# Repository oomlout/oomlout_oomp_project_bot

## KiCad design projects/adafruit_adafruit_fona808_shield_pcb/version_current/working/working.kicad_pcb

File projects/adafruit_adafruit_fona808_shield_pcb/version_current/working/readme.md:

# OOMP Project  
## Adafruit-FONA808-Shield-PCB  by adafruit  
  
oomp key: oomp_projects_flat_adafruit_adafruit_fona808_shield_pcb  
(snippet of original readme)  
  
-- Adafruit FONA808 Shield PCB  
  
<a href="http://www.adafruit.com/products/2636"><br/>  
Click here to purchase one from the Adafruit shop</a>  
  
PCB files for the Adafruit FONA808 Shield. Format is EagleCAD schematic and board layout  
* https://www.adafruit.com/products/2636  
  
--- DESCRIPTION  
Cellular + GPS tracking, all in one, for your Arduino? Oh yes! Introducing Adafruit FONA 808 GSM + GPS Shield, an all-in-one cellular phone module with that lets you add location-tracking, voice, text, SMS and data to your project, in Arduino shield format for easy use.  
  
If you want a version without GPS, check out the FONA 800 Shield [here](https://www.adafruit.com/product/2468).  
  
If you don't need the shield format, we also have this is a petite breakout [here](https://www.adafruit.com/product/2542).  
  
If you just want a plain FONA, [click here](https://www.adafruit.com/product/1946).  
  
This shield fits right over your Arduino or compatible. At the heart is a powerful GSM cellular module (we use the latest SIM808) with integrated GPS. This module can do just about everything  
  
- Quad-band 850/900/1800/1900MHz - connect onto any global GSM network with any 2G SIM (in the USA, T-Mobile is suggested)  
- Fully-integrated GPS (MT3337 chipset with -165 dBm tracking sensitivity) that can be controlled and query over the same serial port  
- Make and receive voice calls using a headset or an external 32Ω speaker + electret microphone  
- Send and receive SM  
  full source readme at [readme_src.md](readme_src.md)  
  
source repo at: [https://github.com/adafruit/Adafruit-FONA808-Shield-PCB](https://github.com/adafruit/Adafruit-FONA808-Shield-PCB)  
## Board  

## Schematic  

[schematic pdf](working_schematic.pdf)  
## Images

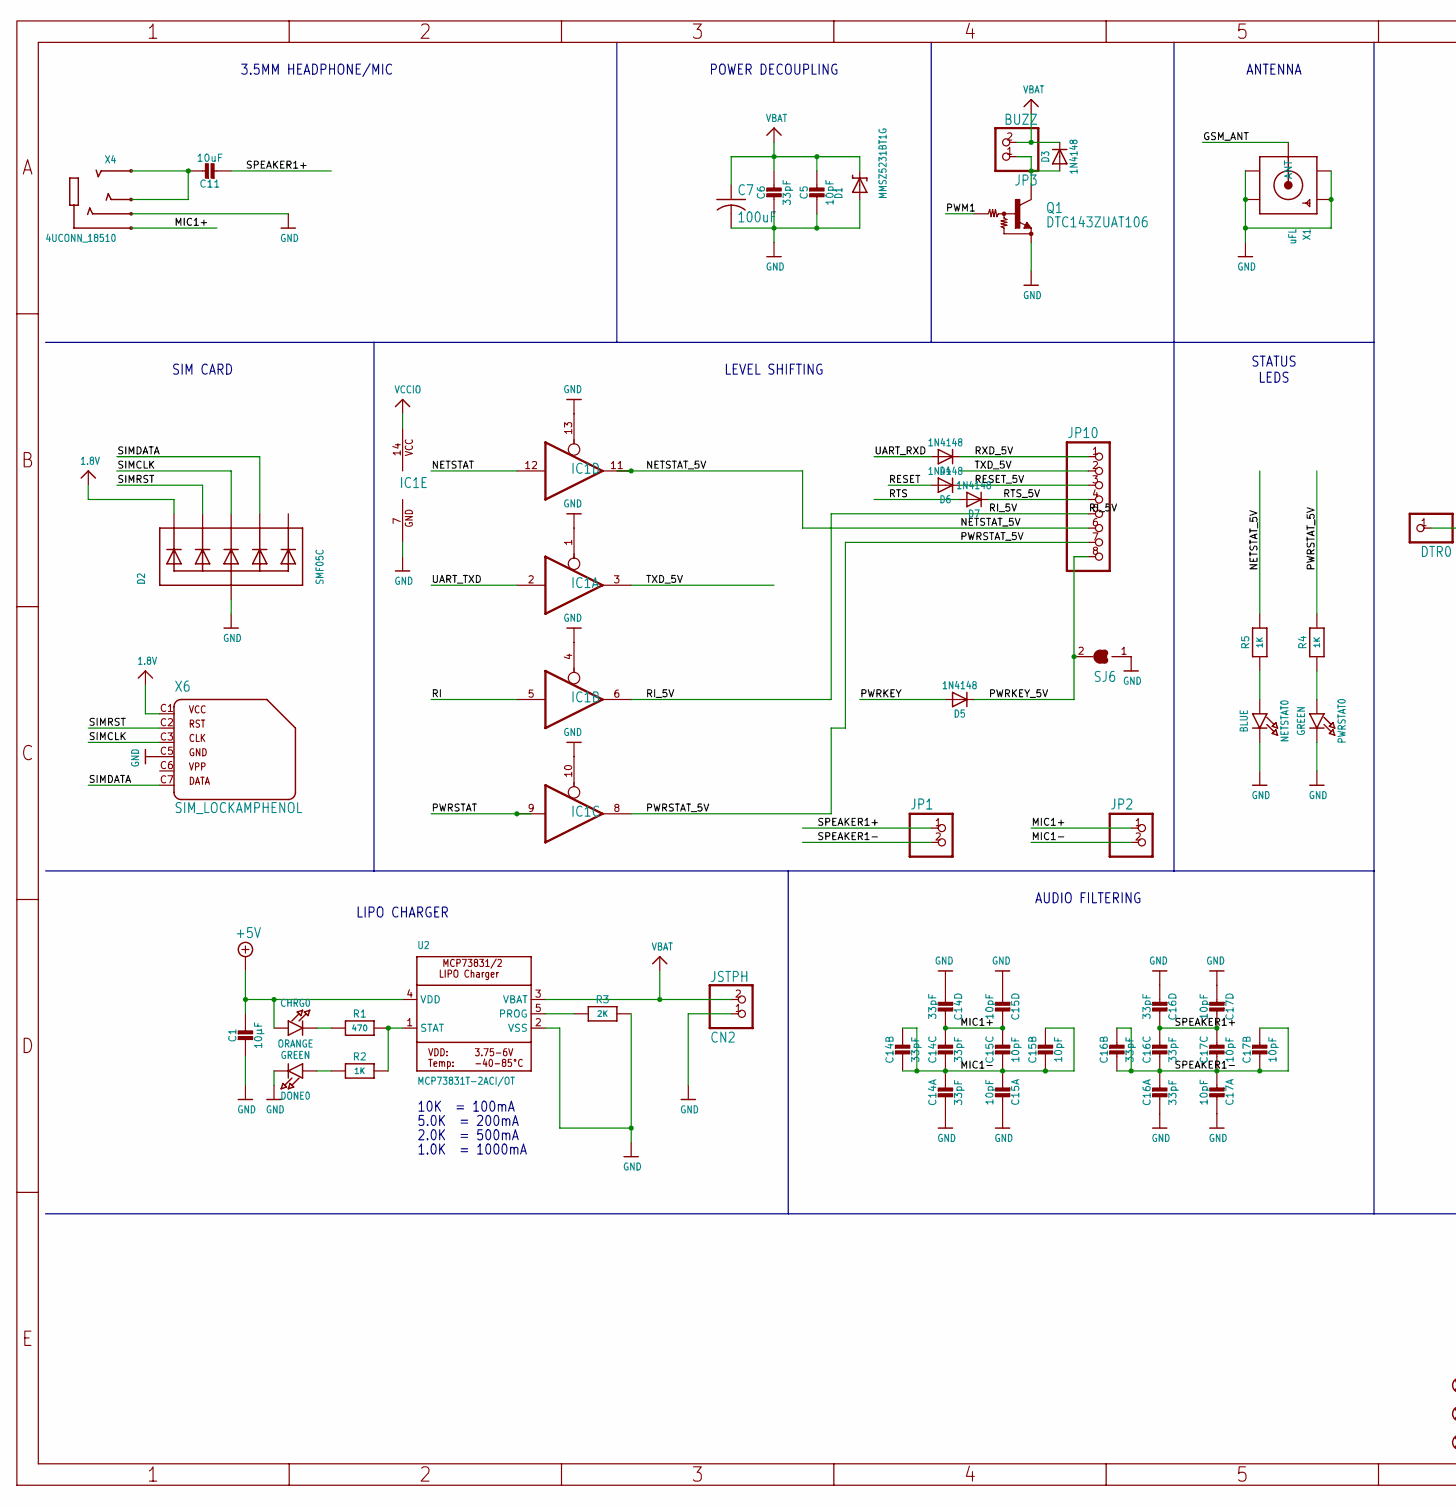
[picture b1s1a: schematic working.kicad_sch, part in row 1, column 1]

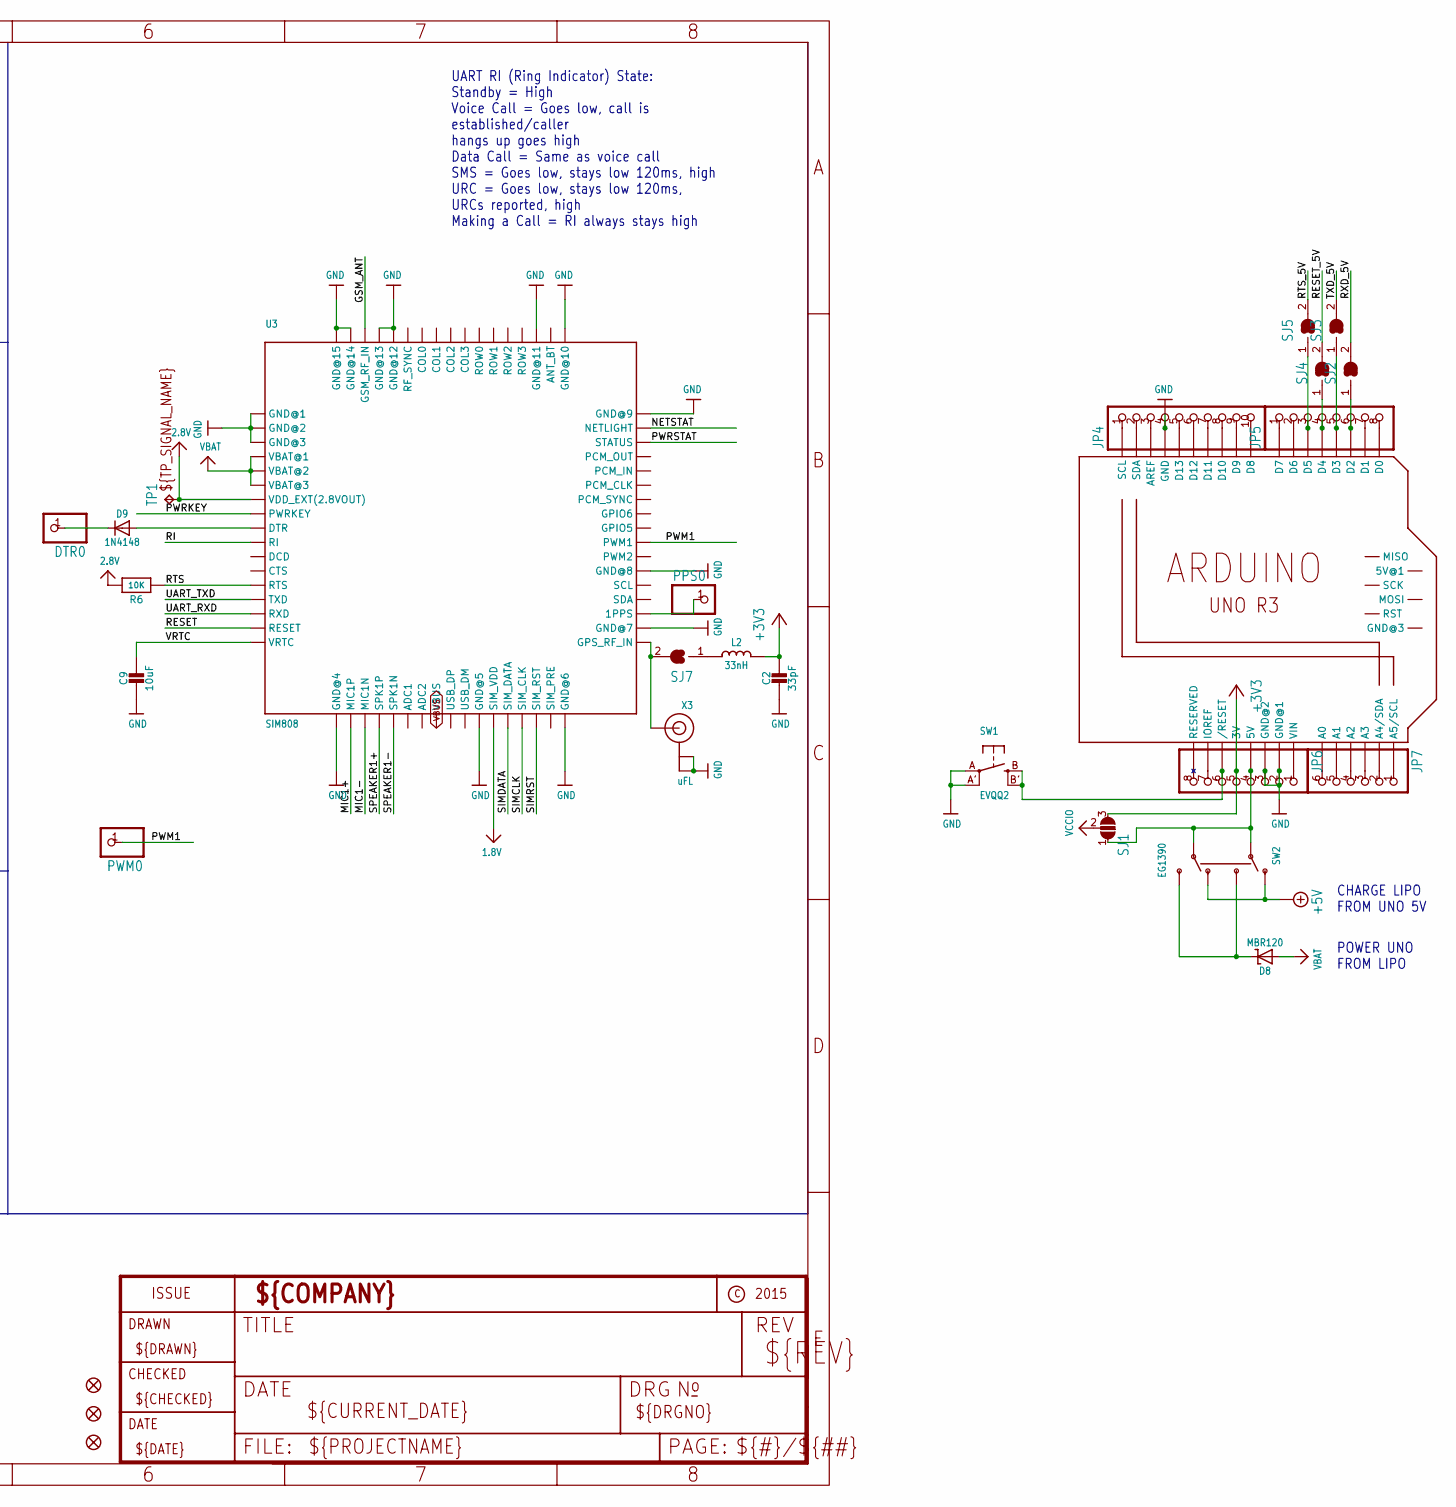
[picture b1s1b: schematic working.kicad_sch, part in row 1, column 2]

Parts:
C1: 10µF; 0805-NO
C2, C6: 33pF; 0805-NO
C5: 10pF; 0805-NO
C7: 100uF; C1210
C9, C11: 10uF; 0805-NO
C14, C16: 33pF; RESPACK_4X0603
C15, C17: 10pF; RESPACK_4X0603
CHRG0: ORANGE; CHIPLED_0805_NOOUTLINE
CN2: JSTPH; JSTPH2
D1: MMSZ5231BT1G; SOD-123
D2: SMF05C; SOT363
D3, D4, D5, D6, D7, D9: 1N4148; SOD-323
D8: MBR120; SOD-123
DONE0: GREEN; CHIPLED_0805_NOOUTLINE
DTR0: PINHD-1X1CB; 1X01-CLEANBIG
FID1, FID2, FID3: FIDUCIAL""; FIDUCIAL_1MM
IC1: 74125PW; TSSOP14
JP1, JP2: HEADER-1X2ROUND; 1X02_ROUND
JP3: BUZZ; 1X02_ROUND
JP4: HEADER-1X1070MIL; 1X10_ROUND70
JP5, JP6: HEADER-1X876MIL; 1X08_ROUND_76
JP7: HEADER-1X676MIL; 1X06_ROUND_76
JP10: HEADER-1X870MIL; 1X08_ROUND_70
L2: 33nH; _0805MP
M1: ARDUINO_R3_ICSP_NODIM; ARDUINOR3_ICSP_NODIM
NETSTAT0: BLUE; CHIPLED_0805_NOOUTLINE
PPS0: PINHD-1X1CB; 1X01-CLEANBIG
PWM0: PINHD-1X1CB; 1X01-CLEANBIG
PWRSTAT0: GREEN; CHIPLED_0805_NOOUTLINE
Q1: DTC143ZUAT106; SC59-BEC
R1: 470; 0805-NO
R2, R4, R5: 1K; 0805-NO
R3: 2K; 0805-NO
R6: 10K; 0805-NO
SJ1: SOLDERJUMPER_2WAY; SOLDERJUMPER_2WAY_OPEN_NOPASTE
SJ2, SJ3, SJ4, SJ5, SJ6: SOLDERJUMPER_CLOSED; SOLDERJUMPER_CLOSEDWIRE
SJ7: SOLDERJUMPER; SOLDERJUMPER_ARROW_NOPASTE
SW1: EVQQ2; EVQ-Q2
SW2: EG1390
TP1: TPTP11R; TP11R
U2: MCP73831T-2ACI/OT; SOT23-5
U3: SIM808; SIM900_SMT
X1: uFL; SMA_EDGELAUNCH_UFL
X3: uFL; U.FL
X4: 4UCONN_18510
X6: SIM_LOCKAMPHENOL; C707_10M006_512_2

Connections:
1.8V: D2.1 (C1), U3.P$29 (SIM_VDD), X6.C1 (1)
2.8V: R6.2, TP1.TP, U3.P$7 (VDD_EXT(2.8VOUT))
5V: JP6.4, M1.5V, SJ1.1, SW2.P1, SW2.P2
+3V3: C2.1, JP6.5, L2.2, M1.3V, SJ1.3
+5V: C1.1, CHRG0.A, SW2.O1, SW2.O2, U2.4 (VDD)
A0: JP7.6, M1.A0
A1: JP7.5, M1.A1
A2: JP7.4, M1.A2
A3: JP7.3, M1.A3
A4: JP7.2, M1.A4 (A4/SDA)
A5: JP7.1, M1.A5 (A5/SCL)
AREF: JP4.3, M1.AREF
BUZZ-: D3.A, JP3.1, Q1.C
D0: JP5.8, M1.D0
D1: JP5.7, M1.D1
D2: JP5.6, M1.D2, SJ2.1
D3: JP5.5, M1.D3, SJ3.1
D4: JP5.4, M1.D4, SJ4.1
D5: JP5.3, M1.D5, SJ5.1
D6: JP5.2, M1.D6
D7: JP5.1, M1.D7
D8: JP4.10, M1.D8
D9: JP4.9, M1.D9
D10: JP4.8, M1.D10
D11: JP4.7, M1.D11
D12: JP4.6, M1.D12
D13: JP4.5, M1.D13
DTR_5V: D9.C, DTR0.1
GND: C1.2, C2.2, C5.2, C6.2, C7.2, C9.2, C14.5 (2), C14.8 (2), C15.4 (1), C15.8 (2), C16.5 (2), C16.8 (2), C17.4 (1), C17.8 (2), CN2.1, D1.A, D2.2 (A), DONE0.C, IC1.1 (OE), IC1.4 (OE), IC1.7 (GND), IC1.10 (OE), IC1.13 (OE), JP4.4, JP6.2, JP6.3, M1.GND, M1.GND@1 (GND@2), M1.GND@3 (GND@1), NETSTAT0.C, PWRSTAT0.C, Q1.E, R3.2, SJ6.1, SW1.A, SW1.A' (P1), U2.2 (VSS), U3.P$1 (GND@1), U3.P$2 (GND@2), U3.P$3 (GND@3), U3.P$18 (GND@4), U3.P$28 (GND@5), U3.P$34 (GND@6), U3.P$36 (GND@7), U3.P$40 (GND@8), U3.P$51 (GND@9), U3.P$52 (GND@10), U3.P$54 (GND@11), U3.P$64 (GND@12), U3.P$65 (GND@13), U3.P$67 (GND@14), U3.P$68 (GND@15), X1.GND@1 (GND1), X1.GND@2 (GND2), X1.GND@3 (GND3), X1.GND@4 (GND4), X3.1 (GND@0), X3.2 (GND@1), X4.4-INNER_SLEEVE (RING1), X6.C5 (4)
GPS_PPS: PPS0.1, U3.P$37 (1PPS)
GSM_ANT: U3.P$66 (GSM_RF_IN), X1.P (ANT)
HP+: C11.1, X4.2-TIP (RING3), X4.3-OUTER_SLEEVE (RING2)
IOREF: JP6.7, M1.IOREF
MIC1+: C14.1, C14.2 (1), C15.1, C15.2 (1), JP2.1, U3.P$19 (MIC1P), X4.1-GND (TIP)
MIC1-: C14.3 (1), C14.4 (1), C14.6 (2), C14.7 (2), C15.3 (1), C15.5 (2), C15.6 (2), C15.7 (2), JP2.2, U3.P$20 (MIC1N)
unnamed: CHRG0.C, R1.1
unnamed: R1.2, R2.2, U2.1 (STAT)
unnamed: SJ7.2, U3.P$35 (GPS_RF_IN), X3.3 (SIGNAL)
unnamed: PWRSTAT0.A, R4.1
unnamed: R3.1, U2.5 (PROG)
unnamed: DONE0.A, R2.1
unnamed: NETSTAT0.A, R5.1
unnamed: D8.C, SW2.S1, SW2.S2
unnamed: L2.1, SJ7.1
unnamed: D9.A, U3.P$9 (DTR)
NC: JP6.8, M1.RESERVED
NETSTAT: IC1.12 (I), U3.P$50 (NETLIGHT)
NETSTAT_5V: IC1.11 (O), JP10.6, R5.2
PWM1: PWM0.1, Q1.B, U3.P$42 (PWM1)
PWRKEY: D5.A, U3.P$8 (PWRKEY)
PWRKEY_5V: D5.C, JP10.8, SJ6.2
PWRSTAT: IC1.9 (I), U3.P$49 (STATUS)
PWRSTAT_5V: IC1.8 (O), JP10.7, R4.2
RESET: D6.A, U3.P$16 (RESET)
RESET_5V: D6.C, JP10.3, SJ4.2
RI: IC1.5 (I), U3.P$10 (RI)
RI_5V: IC1.6 (O), JP10.5
RST: JP6.6, M1.RESET (/RESET), SW1.B (S), SW1.B' (S1)
RTS: D7.A, R6.1, U3.P$13 (RTS)
RTS_5V: D7.C, JP10.4, SJ5.2
RXD_5V: D4.C, JP10.1, SJ2.2
SCL: JP4.1, M1.SCL
SDA: JP4.2, M1.SDA
SIMCLK: D2.4 (C3), U3.P$31 (SIM_CLK), X6.C3 (3)
SIMDATA: D2.5 (C4), U3.P$30 (SIM_DATA), X6.C7 (6)
SIMRST: D2.3 (C2), U3.P$32 (SIM_RST), X6.C2 (2)
SPEAKER1+: C11.2, C16.1, C16.2 (1), C17.1, C17.2 (1), JP1.1, U3.P$21 (SPK1P)
SPEAKER1-: C16.3 (1), C16.4 (1), C16.6 (2), C16.7 (2), C17.3 (1), C17.5 (2), C17.6 (2), C17.7 (2), JP1.2, U3.P$22 (SPK1N)
TXD_5V: IC1.3 (O), JP10.2, SJ3.2
UART_RXD: D4.A, U3.P$15 (RXD)
UART_TXD: IC1.2 (I), U3.P$14 (TXD)
VBAT: C5.1, C6.1, C7.1, CN2.2, D1.C, D3.C, D8.A, JP3.2, U2.3 (VBAT), U3.P$4 (VBAT@1), U3.P$5 (VBAT@2), U3.P$6 (VBAT@3)
VBUS: U3.P$25 (VBUS)
VCCIO: IC1.14 (VCC), SJ1.2
VIN: JP6.1, M1.VIN
VRTC: C9.1, U3.P$17 (VRTC)

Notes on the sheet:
AUDIO FILTERING
LIPO CHARGER
CHARGE LIPO FROM UNO 5V
POWER UNO FROM LIPO
LEVEL SHIFTING
10K = 100mA
1.0K = 1000mA
2.0K = 500mA
STATUS LEDS
SIM CARD
5.0K = 200mA
ANTENNA
3.5MM HEADPHONE/MIC
POWER DECOUPLING
UART RI (Ring Indicator) State: Standby = High Voice Call = Goes low, call is established/caller hangs up goes high Data Call = Same as voice call SMS = Goes low, stays low 120ms, high URC = Goes low, stays low 120ms, URCs reported, high Making a Call = RI always stays high

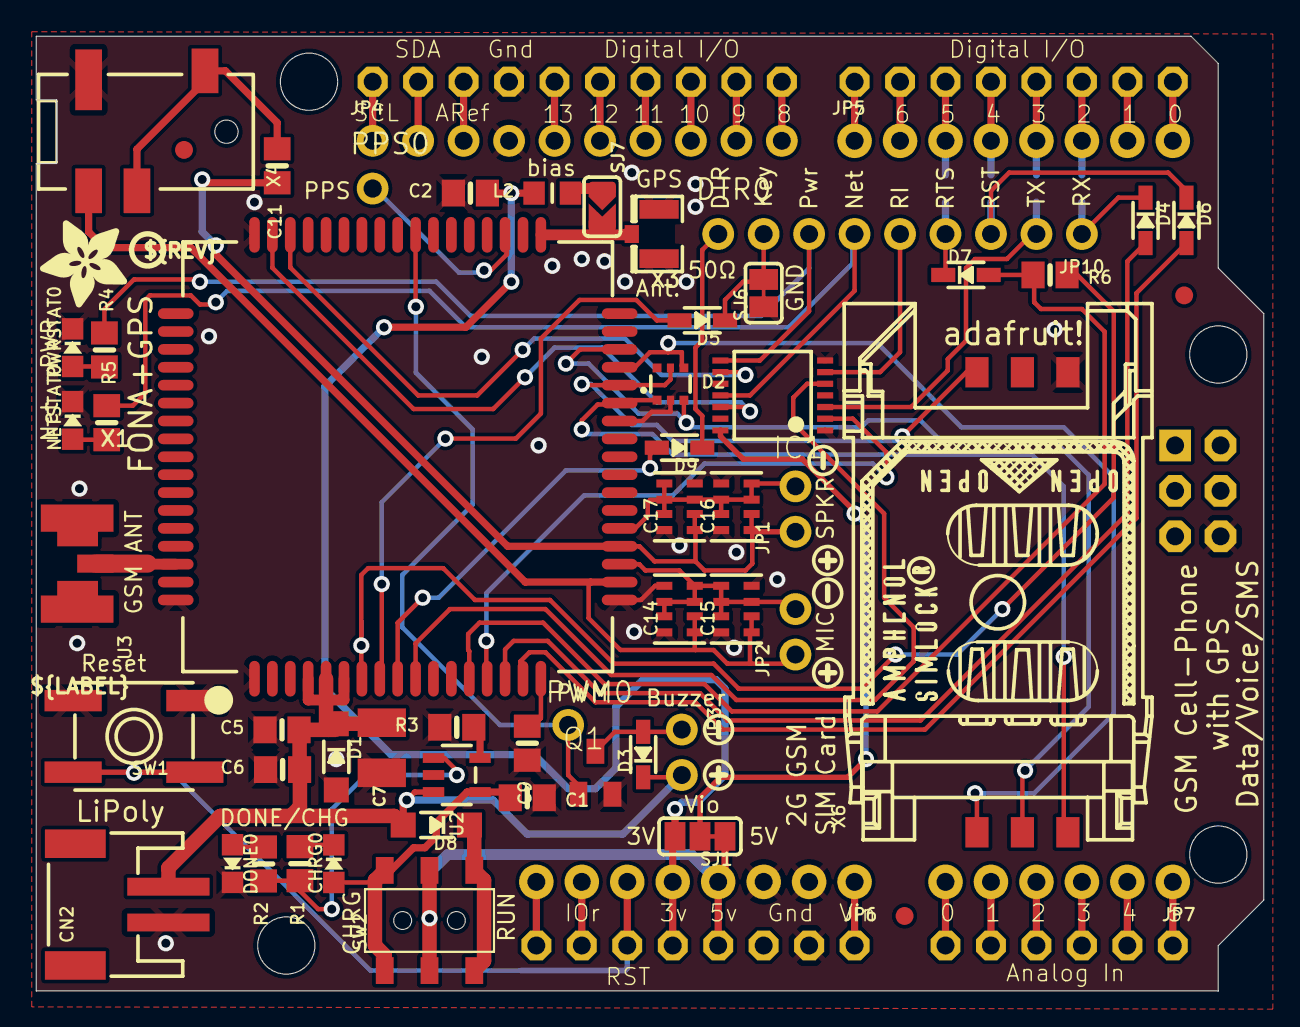
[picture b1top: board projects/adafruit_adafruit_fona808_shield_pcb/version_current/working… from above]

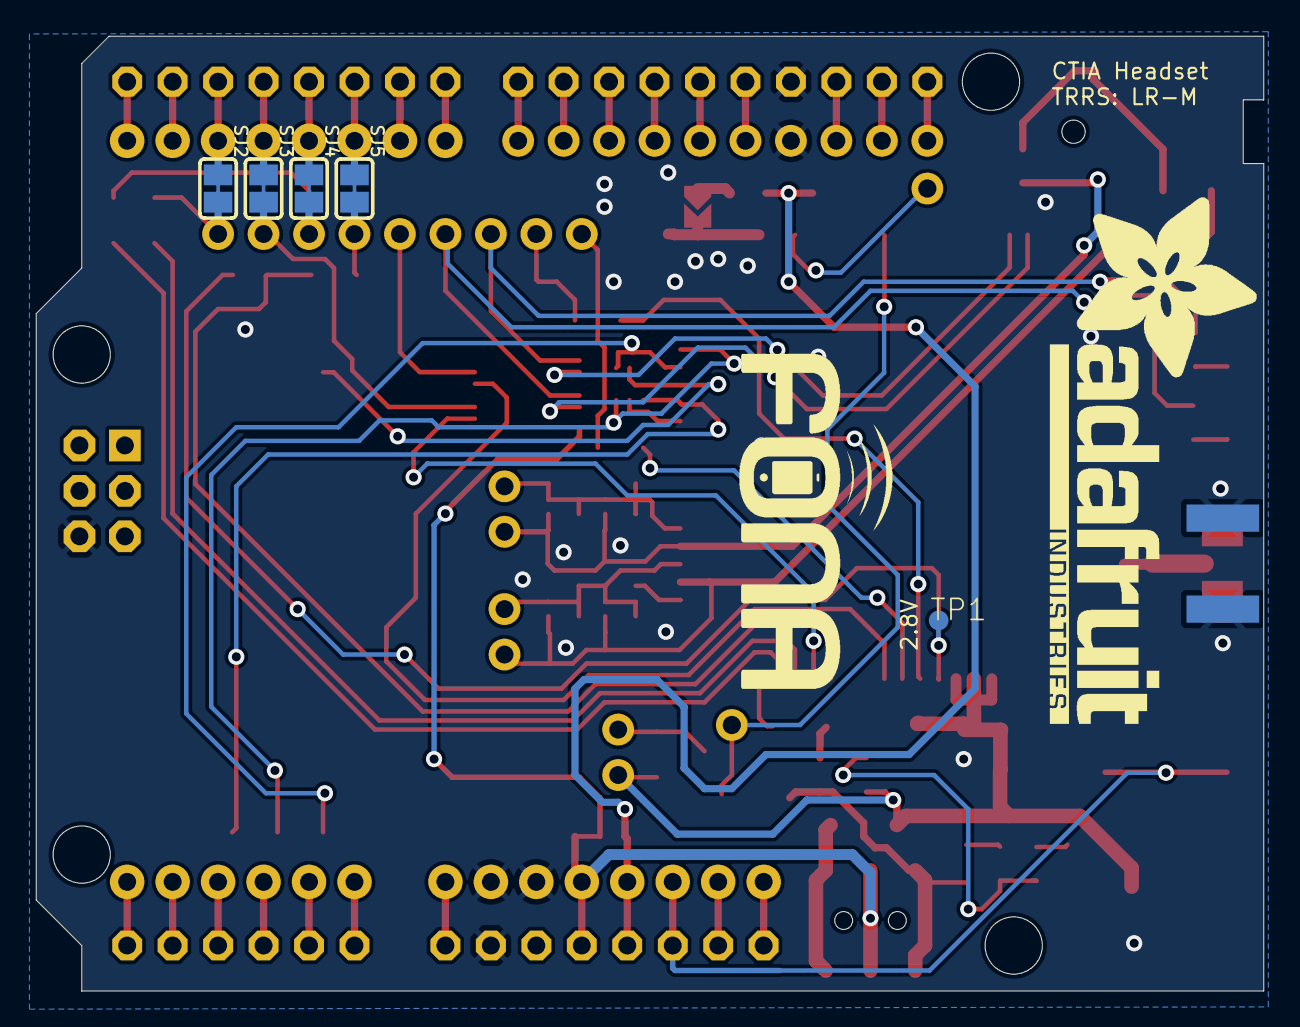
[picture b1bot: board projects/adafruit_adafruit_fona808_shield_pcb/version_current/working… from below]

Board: 2 copper layers, 68.6 x 53.3 mm, 79 parts (7 on the bottom side), 75 nets.

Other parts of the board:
@HOLE0, @HOLE1, @HOLE2, @HOLE3: (no value)
U$2, U$20, U$35: SYMBOL_PLUS
U$25: ADAFRUIT_TEXT_30MM
U$26: FONA_LOGO
U$33, U$34, U$41: SYMBOL_MINUS
U$36: ADAFRUIT_5MM
U$64: PCBFEAT-REV-040

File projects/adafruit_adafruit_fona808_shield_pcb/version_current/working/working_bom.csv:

Row,Description,Part,References,Value,Footprint,Quantity Per PCB,Status,Datasheet
1,,CAP_4PACK1206,C15 C17,10pF,RESPACK_4X0603,2, ,
2,,CAP_CERAMIC0805-NOOUTLINE,C5,10pF,0805-NO,1, ,
3,,CAP_4PACK1206,C14 C16,33pF,RESPACK_4X0603,2, ,
4,,CAP_CERAMIC0805-NOOUTLINE,C2 C6,33pF,0805-NO,2, ,
5,,CAP_CERAMIC0805-NOOUTLINE,C1 C9 C11,10µF,0805-NO,3, ,
6,,C-USC1210,C7,100uF,C1210,1, ,
7,,LED0805_NOOUTLINE,CHRG0,ORANGE,CHIPLED_0805_NOOUTLINE,1, ,
8,,JST_2PIN,CN2,JSTPH,JSTPH2,1, ,
9,,DIODESOD-323,D3 D4 D5 D6 D7 D9,1N4148,SOD-323,6, ,
10,,DIODE-SCHOTTKYSOD-123,D8,MBR120,SOD-123,1, ,
11,,DIODE-ZENERSOD123,D1,MMSZ5231BT1G,SOD-123,1, ,
12,,TVSARRAY_5LANE,D2,SMF05C,SOT363,1, ,
13,,LED0805_NOOUTLINE,DONE0 PWRSTAT0,GREEN,CHIPLED_0805_NOOUTLINE,2, ,
14,,PINHD-1X1CB,DTR0 PPS0 PWM0,PINHD-1X1CB,1X01-CLEANBIG,3, ,
15,,74125PW,IC1,74125PW,TSSOP14,1, ,
16,,HEADER-1X2ROUND,JP3,BUZZ,1X02_ROUND,1, ,
17,,HEADER-1X1070MIL,JP4,HEADER-1X1070MIL,1X10_ROUND70,1, ,
18,,HEADER-1X2ROUND,JP1 JP2,HEADER-1X2ROUND,1X02_ROUND,2, ,
19,,HEADER-1X676MIL,JP7,HEADER-1X676MIL,1X06_ROUND_76,1, ,
20,,HEADER-1X870MIL,JP10,HEADER-1X870MIL,1X08_ROUND_70,1, ,
21,,HEADER-1X876MIL,JP5 JP6,HEADER-1X876MIL,1X08_ROUND_76,2, ,
22,,INDUCTOR_0805MP,L2,33nH,_0805MP,1, ,
23,,ARDUINO_R3_ICSP_NODIM,M1,ARDUINO_R3_ICSP_NODIM,ARDUINOR3_ICSP_NODIM,1, ,
24,,LED0805_NOOUTLINE,NETSTAT0,BLUE,CHIPLED_0805_NOOUTLINE,1, ,
25,,-NPN_DRIVER-SC59-BEC,Q1,DTC143ZUAT106,SC59-BEC,1, ,
26,,RESISTOR0805_NOOUTLINE,R1,470,0805-NO,1, ,
27,,RESISTOR0805_NOOUTLINE,R2 R4 R5,1K,0805-NO,3, ,
28,,RESISTOR0805_NOOUTLINE,R3,2K,0805-NO,1, ,
29,,RESISTOR0805_NOOUTLINE,R6,10K,0805-NO,1, ,
30,,SWITCH_DPDTEG1390,SW2,EG1390,EG1390,1, ,
31,,SWITCH_TACT_SMT,SW1,EVQQ2,EVQ-Q2,1, ,
32,,MCP73831/2,U2,MCP73831T-2ACI/OT,SOT23-5,1, ,
33,,GSM_SIM808_LITERAL,U3,SIM808,SIM900_SMT,1, ,
34,,AUDIO_3.5MMJACK_4POL,X4,4UCONN_18510,4UCONN_18510,1, ,
35,,SIM_LOCKAMPHENOL,X6,SIM_LOCKAMPHENOL,C707_10M006_512_2,1, ,
36,,SMACONNECTOR_EDGE_UFL,X1,uFL,SMA_EDGELAUNCH_UFL,1, ,
37,,ANTENNA_U.FL,X3,uFL,U.FL,1, ,





Project info:
Schematic:,working
Variant:,default
Revision:,
Date:,2023-08-02_17-08-33
KiCad Version:,7.0.6-7.0.6~ubuntu22.04.1
Statistics:
Component Groups:,37
Component Count:,54 (0 SMD/ 0 THT)
Fitted Components:,54 (0 SMD/ 0 THT)
Number of PCBs:,1
Total Components:,54

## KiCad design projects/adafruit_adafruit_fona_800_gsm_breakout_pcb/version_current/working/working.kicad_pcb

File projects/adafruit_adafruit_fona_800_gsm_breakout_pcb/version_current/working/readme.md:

# Adafruit-FONA-800-GSM-Breakout-PCB by adafruit  
This is a harvested standardized copy of a project from github.  
The original project can be found at:  
https://github.com/adafruit/Adafruit-FONA-800-GSM-Breakout-PCB  
Please consult that link for additional, details, files, and license information.  
Note: It was auto harvested and if the original repo had more than one board file or anything out of the ordinary the files here are likely not representative.

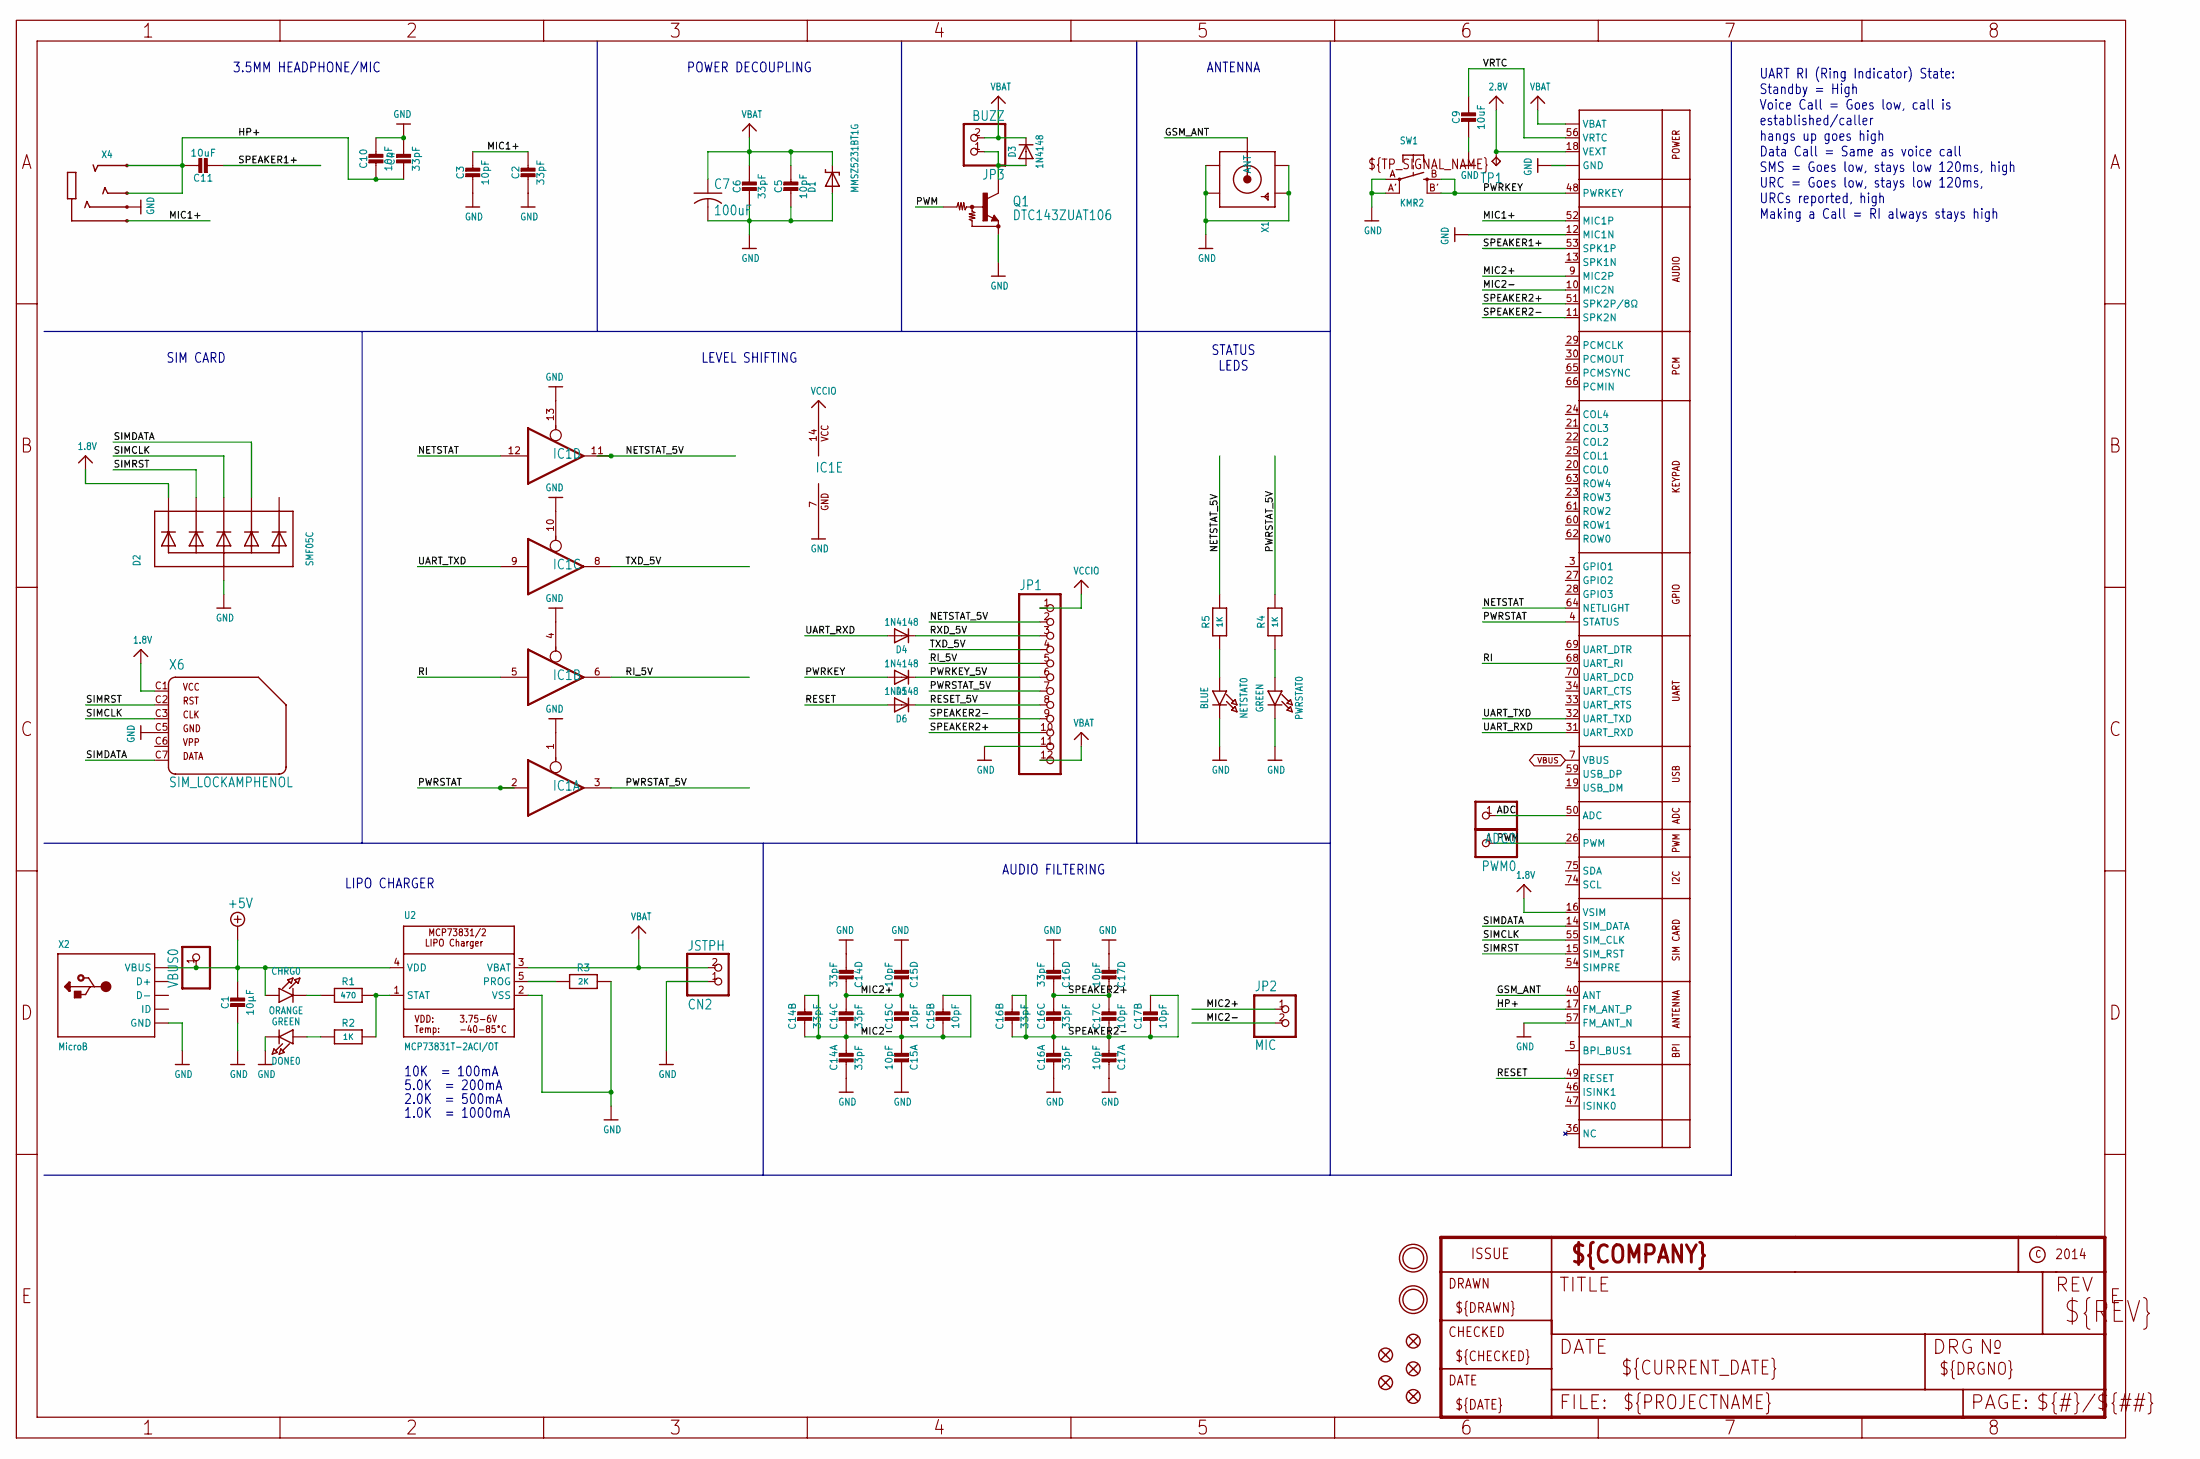
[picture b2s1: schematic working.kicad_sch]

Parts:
ADC0: PINHD-1X1CB; 1X01-CLEANBIG
C1: 10µF; 0805-NO
C2, C4, C6: 33pF; 0805-NO
C3, C5, C10: 10pF; 0805-NO
C7: 100uF; C1210
C9, C11: 10uF; 0805-NO
C14, C16: 33pF; RESPACK_4X0603
C15, C17: 10pF; RESPACK_4X0603
CHRG0: ORANGE; CHIPLED_0805_NOOUTLINE
CN2: JSTPH; JSTPH2
D1: MMSZ5231BT1G; SOD-123
D2: SMF05C; SOT363
D3, D4, D5, D6: 1N4148; SOD-323
DONE0: GREEN; CHIPLED_0805_NOOUTLINE
FID1, FID2, FID3, FID4, FID5: FIDUCIAL""; FIDUCIAL_1MM
IC1: 74125PW; TSSOP14
JP1: PINHD-1X12-CB; 1X12-CB
JP2: MIC; 1X02_ROUND
JP3: BUZZ; 1X02_ROUND
NETSTAT0: BLUE; CHIPLED_0805_NOOUTLINE
PWM0: PINHD-1X1CB; 1X01-CLEANBIG
PWRSTAT0: GREEN; CHIPLED_0805_NOOUTLINE
Q1: DTC143ZUAT106; SC59-BEC
R1: 470; 0805-NO
R2, R4, R5: 1K; 0805-NO
R3: 2K; 0805-NO
SW1: KMR2; BTN_KMR2_4.6X2.8
TP1: TPTP11R; TP11R
U1: SIM800H/L; SIM800L
U2: MCP73831T-2ACI/OT; SOT23-5
U$33, U$34: MOUNTINGHOLE2.5; MOUNTINGHOLE_2.5_PLATED
VBUS0: PINHD-1X1CB; 1X01-CLEANBIG
X1: SMACONNECTOR_EDGE_UFL; SMA_EDGELAUNCH_UFL
X2: MicroB; 4UCONN_20329
X4: AUDIO_3.5MMJACK_4POL; 4UCONN_18510
X6: SIM_LOCKAMPHENOL; C707_10M006_512_2

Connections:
1.8V: D2.1 (C1), U1.16 (VSIM), X6.C1 (1)
2.8V: TP1.TP, U1.18 (VEXT)
+5V: C1.1, CHRG0.A, U2.4 (VDD), VBUS0.1, X2.VBUS
ADC: ADC0.1, U1.50 (ADC)
GND: C1.2, C2.2, C3.2, C4.1, C5.2, C6.2, C7.2, C9.2, C10.1, C14.5 (2), C14.8 (2), C15.4 (1), C15.8 (2), C16.5 (2), C16.8 (2), C17.4 (1), C17.8 (2), CN2.1, D1.A, D2.2 (A), DONE0.C, IC1.1 (OE), IC1.4 (OE), IC1.7 (GND), IC1.10 (OE), IC1.13 (OE), JP1.11, NETSTAT0.C, PWRSTAT0.C, Q1.E, R3.2, SW1.A, SW1.A' (P1), U1.2 (GND), U1.6 (GND), U1.8 (GND), U1.12 (MIC1N), U1.35 (GND), U1.37 (GND), U1.38 (GND), U1.39 (GND), U1.41 (GND), U1.43 (GND), U1.44 (GND), U1.45 (GND), U1.57 (FM_ANT_N), U1.58 (GND), U1.67 (GND), U1.71 (GND), U1.72 (GND), U1.73 (GND), U1.76 (GND), U1.77 (GND), U1.78 (GND), U1.79 (GND), U1.80 (GND), U1.81 (GND), U1.82 (GND), U1.83 (GND), U1.84 (GND), U1.85 (GND), U1.86 (GND), U1.87 (GND), U1.88 (GND), U2.2 (VSS), X1.GND@1 (GND1), X1.GND@2 (GND2), X1.GND@3 (GND3), X1.GND@4 (GND4), X2.BASE@1 (GND), X2.BASE@2 (GND), X2.GND, X2.SPRT@1 (GND), X2.SPRT@2 (GND), X2.SPRT@3 (GND), X2.SPRT@4 (GND), X4.4-INNER_SLEEVE (RING1), X6.C5 (4)
GSM_ANT: U1.40 (ANT), X1.P (ANT)
HP+: C4.2, C10.2, C11.1, U1.17 (FM_ANT_P), X4.2-TIP (RING3), X4.3-OUTER_SLEEVE (RING2)
MIC1+: C2.1, C3.1, U1.52 (MIC1P), X4.1-GND (TIP)
MIC2+: C14.1, C14.2 (1), C15.1, C15.2 (1), JP2.1, U1.9 (MIC2P)
MIC2-: C14.3 (1), C14.4 (1), C14.6 (2), C14.7 (2), C15.3 (1), C15.5 (2), C15.6 (2), C15.7 (2), JP2.2, U1.10 (MIC2N)
unnamed: CHRG0.C, R1.1
unnamed: R1.2, R2.2, U2.1 (STAT)
unnamed: PWRSTAT0.A, R4.1
unnamed: R3.1, U2.5 (PROG)
unnamed: DONE0.A, R2.1
unnamed: NETSTAT0.A, R5.1
unnamed: D3.A, JP3.1, Q1.C
NETSTAT: IC1.12 (I), U1.64 (NETLIGHT)
NETSTAT_5V: IC1.11 (O), JP1.2, R5.2
PWM: PWM0.1, Q1.B, U1.26 (PWM)
PWRKEY: D5.A, SW1.B (S), SW1.B' (S1), U1.48 (PWRKEY)
PWRKEY_5V: D5.C, JP1.6
PWRSTAT: IC1.2 (I), U1.4 (STATUS)
PWRSTAT_5V: IC1.3 (O), JP1.7, R4.2
RESET: D6.A, U1.49 (RESET)
RESET_5V: D6.C, JP1.8
RI: IC1.5 (I), U1.68 (UART_RI)
RI_5V: IC1.6 (O), JP1.5
RXD_5V: D4.C, JP1.3
SIMCLK: D2.4 (C3), U1.55 (SIM_CLK), X6.C3 (3)
SIMDATA: D2.5 (C4), U1.14 (SIM_DATA), X6.C7 (6)
SIMRST: D2.3 (C2), U1.15 (SIM_RST), X6.C2 (2)
SPEAKER1+: C11.2, U1.53 (SPK1P)
SPEAKER2+: C16.1, C16.2 (1), C17.1, C17.2 (1), JP1.10, U1.51 (SPK2P/8Ω)
SPEAKER2-: C16.3 (1), C16.4 (1), C16.6 (2), C16.7 (2), C17.3 (1), C17.5 (2), C17.6 (2), C17.7 (2), JP1.9, U1.11 (SPK2N)
TXD_5V: IC1.8 (O), JP1.4
UART_RXD: D4.A, U1.31 (UART_RXD)
UART_TXD: IC1.9 (I), U1.32 (UART_TXD)
VBAT: C5.1, C6.1, C7.1, CN2.2, D1.C, D3.C, JP1.12, JP3.2, U1.1 (VBAT), U1.42 (VBAT), U2.3 (VBAT)
VBUS: U1.7 (VBUS)
VCCIO: IC1.14 (VCC), JP1.1
VRTC: C9.1, U1.56 (VRTC)

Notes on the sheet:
2.0K = 500mA
3.5MM HEADPHONE/MIC
10K = 100mA
AUDIO FILTERING
POWER DECOUPLING
LIPO CHARGER
UART RI (Ring Indicator) State: Standby = High Voice Call = Goes low, call is established/caller hangs up goes high Data Call = Same as voice call SMS = Goes low, stays low 120ms, high URC = Goes low, stays low 120ms, URCs reported, high Making a Call = RI always stays high
5.0K = 200mA
SIM CARD
1.0K = 1000mA
LEVEL SHIFTING
ANTENNA
STATUS LEDS

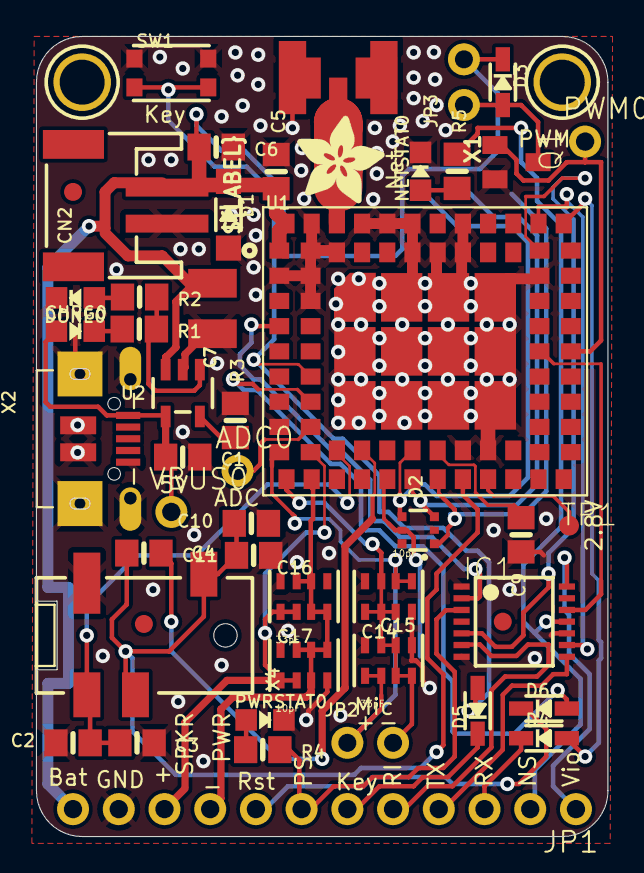
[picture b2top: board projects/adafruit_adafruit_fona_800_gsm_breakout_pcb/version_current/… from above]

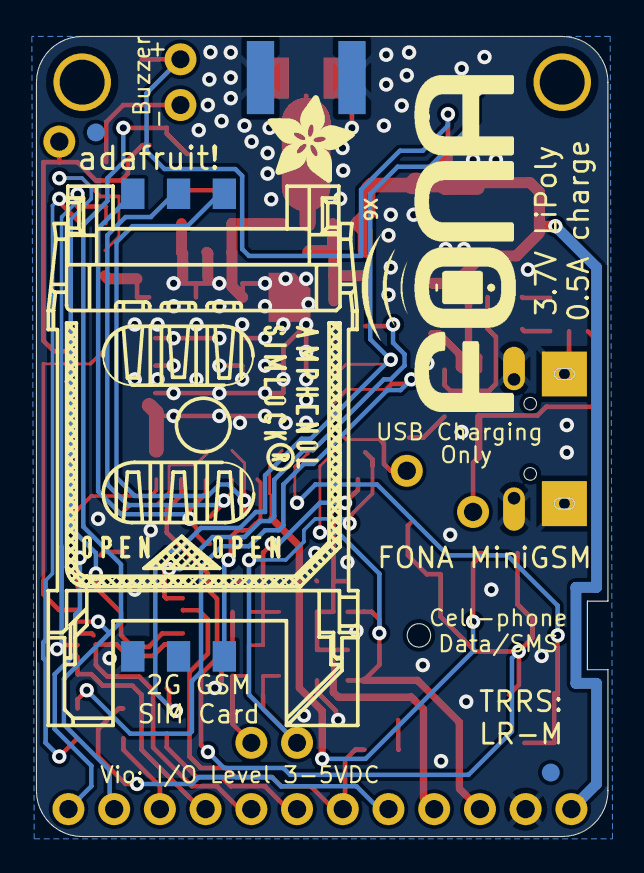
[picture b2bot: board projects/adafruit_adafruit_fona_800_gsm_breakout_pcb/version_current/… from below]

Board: 2 copper layers, 31.8 x 44.5 mm, 56 parts (5 on the bottom side), 41 nets.

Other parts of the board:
U$10, U$36: ADAFRUIT_5MM
U$26: FONA_LOGO

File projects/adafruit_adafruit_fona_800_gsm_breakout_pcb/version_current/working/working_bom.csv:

Row,Description,Part,References,Value,Footprint,Quantity Per PCB,Status,Datasheet
1,,PINHD-1X1CB,ADC0 PWM0 VBUS0,PINHD-1X1CB,1X01-CLEANBIG,3, ,
2,,CAP_CERAMIC0805-NOOUTLINE,C3 C5 C10,10pF,0805-NO,3, ,
3,,CAP_4PACK1206,C15 C17,10pF,RESPACK_4X0603,2, ,
4,,CAP_4PACK1206,C14 C16,33pF,RESPACK_4X0603,2, ,
5,,CAP_CERAMIC0805-NOOUTLINE,C2 C4 C6,33pF,0805-NO,3, ,
6,,CAP_CERAMIC0805-NOOUTLINE,C1 C9 C11,10µF,0805-NO,3, ,
7,,C-USC1210,C7,100uF,C1210,1, ,
8,,LED0805_NOOUTLINE,CHRG0,ORANGE,CHIPLED_0805_NOOUTLINE,1, ,
9,,JST_2PIN,CN2,JSTPH,JSTPH2,1, ,
10,,DIODESOD-323,D3 D4 D5 D6,1N4148,SOD-323,4, ,
11,,DIODE-ZENERSOD123,D1,MMSZ5231BT1G,SOD-123,1, ,
12,,TVSARRAY_5LANE,D2,SMF05C,SOT363,1, ,
13,,LED0805_NOOUTLINE,DONE0 PWRSTAT0,GREEN,CHIPLED_0805_NOOUTLINE,2, ,
14,,74125PW,IC1,74125PW,TSSOP14,1, ,
15,,HEADER-1X2ROUND,JP3,BUZZ,1X02_ROUND,1, ,
16,,HEADER-1X2ROUND,JP2,MIC,1X02_ROUND,1, ,
17,,PINHD-1X12-CB,JP1,PINHD-1X12-CB,1X12-CB,1, ,
18,,LED0805_NOOUTLINE,NETSTAT0,BLUE,CHIPLED_0805_NOOUTLINE,1, ,
19,,-NPN_DRIVER-SC59-BEC,Q1,DTC143ZUAT106,SC59-BEC,1, ,
20,,RESISTOR0805_NOOUTLINE,R1,470,0805-NO,1, ,
21,,RESISTOR0805_NOOUTLINE,R2 R4 R5,1K,0805-NO,3, ,
22,,RESISTOR0805_NOOUTLINE,R3,2K,0805-NO,1, ,
23,,SWITCH_TACT_SMT4.6X2.8,SW1,KMR2,BTN_KMR2_4.6X2.8,1, ,
24,,MCP73831/2,U2,MCP73831T-2ACI/OT,SOT23-5,1, ,
25,,GSM_SIM800L,U1,SIM800H/L,SIM800L,1, ,
26,,AUDIO_3.5MMJACK_4POL,X4,AUDIO_3.5MMJACK_4POL,4UCONN_18510,1, ,
27,,USBMICRO_20329,X2,MicroB,4UCONN_20329,1, ,
28,,SIM_LOCKAMPHENOL,X6,SIM_LOCKAMPHENOL,C707_10M006_512_2,1, ,
29,,SMACONNECTOR_EDGE_UFL,X1,SMACONNECTOR_EDGE_UFL,SMA_EDGELAUNCH_UFL,1, ,





Project info:
Schematic:,working
Variant:,default
Revision:,
Date:,2023-08-02_17-08-33
KiCad Version:,7.0.6-7.0.6~ubuntu22.04.1
Statistics:
Component Groups:,29
Component Count:,45 (0 SMD/ 0 THT)
Fitted Components:,45 (0 SMD/ 0 THT)
Number of PCBs:,1
Total Components:,45
